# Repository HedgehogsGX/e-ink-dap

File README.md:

# e-ink-dap
DIY ESP32-S3 e-paper music player (DAP): firmware, bring-up tests and notes

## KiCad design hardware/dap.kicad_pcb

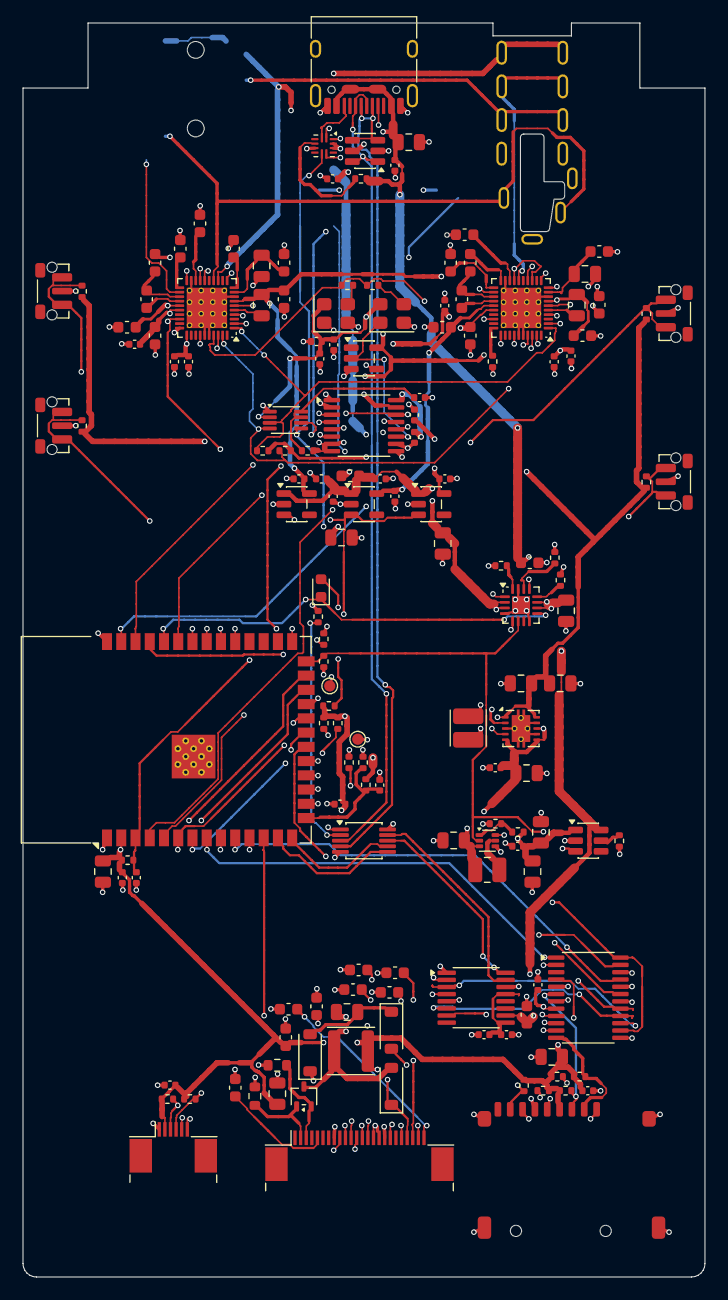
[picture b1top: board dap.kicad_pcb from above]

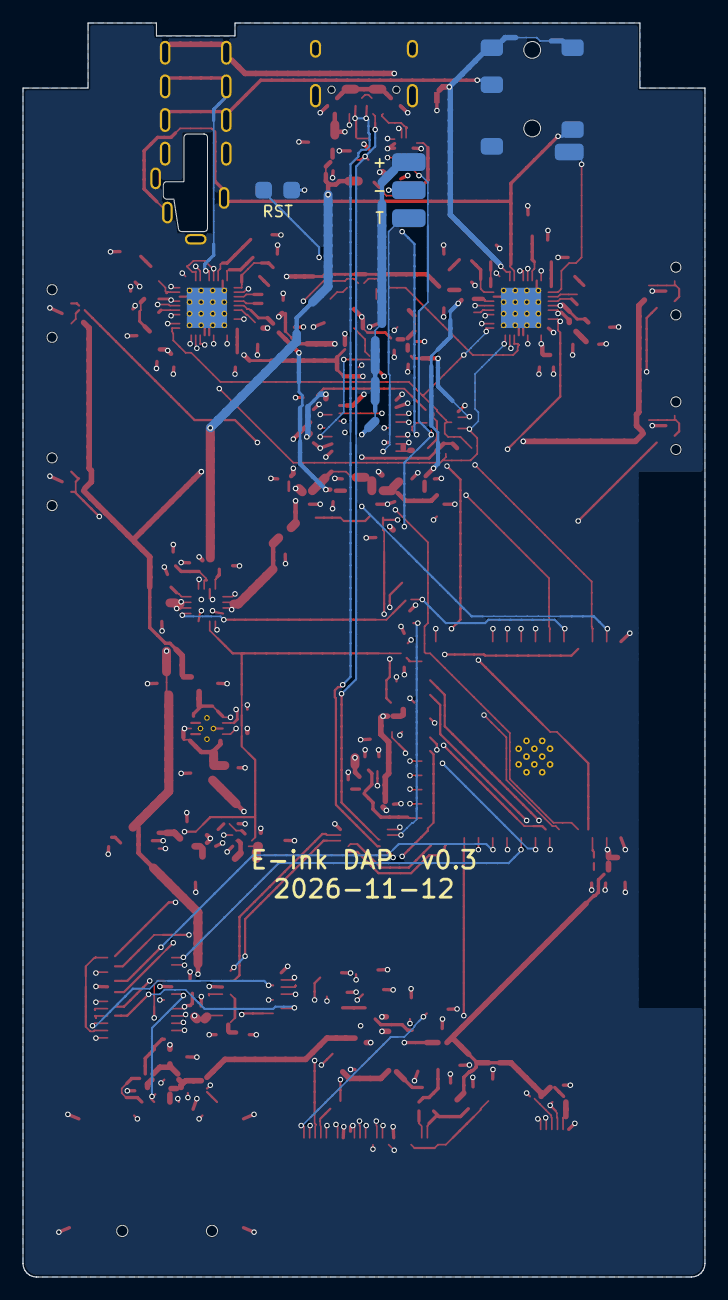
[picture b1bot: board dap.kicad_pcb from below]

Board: 6 copper layers, 60.8 x 111.8 mm, 157 parts (4 on the bottom side), 124 nets.

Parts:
C1: 1uF; C_0603_1608Metric
C2, C3, C4, C14, C15, C19, C34, C42: 10uF; C_0805_2012Metric
C5, C18, C20, C22, C35, C36, C37, C40, C41, C43, C44, C45, C46, C47, C48, C49, C50, C51, C52, C64, C65, C66: 100nF; C_0402_1005Metric
C6, C7, C16, C17, C55, C56, C69, C70: 22uF; C_0805_2012Metric
C8, C9, C10, C11, C12, C13, C21, C33, C39: 1uF; C_0402_1005Metric
C23, C24: 4.7uF/50V; C_0805_2012Metric
C25, C26, C27, C28, C29, C30, C31, C32: 1uF/50V; C_0603_1608Metric
C38, C53, C67: 4.7uF; C_0603_1608Metric
C54, C57, C58, C59, C60, C61, C62, C63, C68, C71, C72, C73, C74, C75, C76, C77: 2.2uF; C_0603_1608Metric
D1: green; LED_0603_1608Metric
D2, D3, D4: MBR0530; D_SOD-123
FB1: 600R@100MHz; L_0603_1608Metric
J1: Battery; Battery_Pads_1x03
J2: E-paper FPC; Jushuo_AFC07-S24FCA-00_1x24-1MP_P0.50_Horizontal
J3: Touch FPC; Jushuo_AFC07-S06FCA-00_1x6-1MP_P0.50_Horizontal
J4: USB-C; USB_C_Receptacle_HRO_TYPE-C-31-M-12
J5: microSD; microSD_TF-01A
J6: PJ-342; Jack_3.5mm_PJ-342
J7: KH-PJ-44002-12DBAP-A; Jack_4.4mm_KH-PJ-44002-12DBAP-A
JP1: Reset; Reset_Pads_1x02
L1: 2.2uH; L_Cenker_CKCS3015
L2: 1uH; L_1008_2520Metric
L3: 10uH; L_Changjiang_FNR4020S
NT1: NetTie; NetTie-2_SMD_Pad0.5mm
Q1: Si1308EDL; SOT-323_SC-70
R1: 1.1k; R_0402_1005Metric
R2: 1.62k; R_0402_1005Metric
R3: 68k; R_0402_1005Metric
R4: 768k; R_0402_1005Metric
R5, R8, R9, R10, R11, R13, R14, R15: 100k; R_0402_1005Metric
R6: 47k; R_0402_1005Metric
R7, R12, R23, R24, R26, R27, R28, R29, R30: 10k; R_0402_1005Metric
R16, R17: 1M; R_0402_1005Metric
R18, R19, R32, R33: 4.7k; R_0402_1005Metric
R20: 1k; R_0402_1005Metric
R21: 1M; R_0603_1608Metric
R22: 0.47; R_0603_1608Metric
R25: 887k; R_0402_1005Metric
R31: 200k; R_0402_1005Metric
R34, R35: 22; R_0402_1005Metric
R36: 4.99k; R_0402_1005Metric
SW1: Play; SW_Push_1P1T-MP_NO_Horizontal_Alps_SKRTLAE010
SW2: Power; SW_Push_1P1T-MP_NO_Horizontal_Alps_SKRTLAE010
SW3: Vol+; SW_Push_1P1T-MP_NO_Horizontal_Alps_SKRTLAE010
SW4: Vol-; SW_Push_1P1T-MP_NO_Horizontal_Alps_SKRTLAE010
TP1: TX; TestPoint_Pad_D1.0mm
TP2: GND; TestPoint_Pad_D1.0mm
U1: BQ24073RGTR; VQFN-16-1EP_3x3mm_P0.5mm_EP1.6x1.6mm
U2: TPS63001DRCR; Texas_DRC0010J_ThermalVias
U3, U4, U5: LP5907MFX-1.8; SOT-23-5
U6: TPS61023DRLR; SOT-563
U7: TPS2553DBVR; SOT-23-6
U8: ESP32-S3-WROOM-1-N16R8; ESP32-S3-WROOM-1
U9: USBLC6-2SC6; SOT-23-6
U10: TUSB320LIRWBR; Texas_X2QFN-12_1.6x1.6mm_P0.4mm
U11: FSUSB42MUX; MSOP-10_3x3mm_P0.5mm
U12: GL823K-HCY04; SSOP-16_3.9x4.9mm_P0.635mm
U13: TS3A27518EPWR; TSSOP-24_4.4x7.8mm_P0.65mm
U14: SN74AVC4T774PWR; TSSOP-16_4.4x5mm_P0.65mm
U15: PCA9306DCUR; VSSOP-8_2.3x2mm_P0.5mm
U16: 74LVC1G04; SOT-23-5
U17, U18: CS43131-CNZR; QFN-40-1EP_5x5mm_P0.4mm_EP3.6x3.6mm_ThermalVias
Y1: 22.5792MHz; Oscillator_SMD_Abracon_ASE-4Pin_3.2x2.5mm
Y2: 24.576MHz; Oscillator_SMD_Abracon_ASE-4Pin_3.2x2.5mm

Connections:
1V8_A: C11.1, C54.1, C55.2, C68.1, C69.2, U3.5, U17.7, U18.7
1V8_CP: C12.1, C59.1, C73.1, U4.5, U17.25, U18.25
1V8_D: C13.1, C45.1, C47.1, C48.1, C49.1, C50.1, C51.1, C64.1, C65.1, R32.1, R33.1, U5.5, U14.15, U15.2, U16.5, U17.4, U17.31, U18.4, U18.31, Y1.4, Y2.4
5V_BOOST: C16.1, C17.1, C18.1, R4.1, U6.6, U7.1
+3V3: C6.1, C7.1, C19.1, C20.1, C23.1, C26.1, C33.1, C36.1, C37.1, C41.1, C42.1, C43.1, C44.1, J2.15, J2.16, J3.2, J5.4, L3.1, R7.1, R12.1, R13.1, R14.1, R15.1, R18.1, R19.1, R20.1, R23.1, R24.1, R26.1, R27.1, R28.1, R29.1, R30.1, R31.1, U2.1, U2.10, U8.2, U10.12, U11.1, U13.8, U14.7, U14.8, U14.16
/Audio/DACL_FILTN: C56.1, U17.6
/Audio/DACL_FILTP: C55.1, U17.5
/Audio/DACL_FLYC_VCP: C62.2, C63.1, U17.23
/Audio/DACL_FLYN_VA: C58.2, U17.11
/Audio/DACL_FLYN_VCP: C63.2, U17.20
/Audio/DACL_FLYP_VA: C58.1, U17.10
/Audio/DACL_FLYP_VCP: C62.1, U17.24
/Audio/DACL_NVA: C56.2, C57.1, U17.9
/Audio/DACL_VCPF_N: C61.1, U17.18
/Audio/DACL_VCPF_P: C60.1, U17.21
/Audio/DACR_ADR: R36.1, U18.30
/Audio/DACR_FILTN: C70.1, U18.6
/Audio/DACR_FILTP: C69.1, U18.5
/Audio/DACR_FLYC_VCP: C76.2, C77.1, U18.23
/Audio/DACR_FLYN_VA: C72.2, U18.11
/Audio/DACR_FLYN_VCP: C77.2, U18.20
/Audio/DACR_FLYP_VA: C72.1, U18.10
/Audio/DACR_FLYP_VCP: C76.1, U18.24
/Audio/DACR_NVA: C70.2, C71.1, U18.9
/Audio/DACR_VCPF_N: C75.1, U18.18
/Audio/DACR_VCPF_P: C74.1, U18.21
/Audio/DET_35: J6.4, U17.22
/Audio/DET_44: J7.11, U18.22
/Audio/HP_GND: J6.2, J6.5, J7.1, J7.6, NT1.1, U17.13, U17.17, U18.13, U18.17
/Audio/I2C_SCL_1V8: R33.2, U15.3, U17.1, U18.1
/Audio/I2C_SDA_1V8: R32.2, U15.4, U17.39, U18.39
/Audio/I2C_VREF2: C46.1, R31.2, U15.7, U15.8
/Audio/LRCK_1V8: U14.13, U17.38, U18.38
/Audio/MCLK: R34.2, R35.2, U17.37, U18.37
/Audio/MCLK_48: R35.1, Y2.3
/Audio/MCLK_441: R34.1, Y1.3
/Audio/OSC_SEL_1V8: U14.11, U16.2, Y2.1
/Audio/OSC_SEL_N: U16.4, Y1.1
/Audio/OUT_LN: J7.4, J7.9, U17.16
/Audio/OUT_LP: J6.3, J7.5, J7.10, U17.14
/Audio/OUT_RN: J7.2, J7.7, U18.16
/Audio/OUT_RP: J6.6, J7.3, J7.8, U18.14
/Audio/SCLK_1V8: U14.14, U17.34, U18.34
/Audio/SDIN_1V8: U14.12, U17.2, U18.2
/Display/EPD_GDR: J2.2, Q1.1, R21.1
/Display/EPD_NEG: C24.2, D3.2, D4.1
/Display/EPD_RESE: J2.3, Q1.2, R22.1
/Display/EPD_SW: C24.1, D2.2, L3.2, Q1.3
/Display/EPD_VCOM: C32.1, J2.24
/Display/EPD_VDD: C27.1, J2.18
/Display/EPD_VGH: C29.1, D2.1, J2.21
/Display/EPD_VGL: C31.1, D4.2, J2.23
/Display/EPD_VSH1: C28.1, J2.20
/Display/EPD_VSH2: C25.1, J2.5
/Display/EPD_VSL: C30.1, J2.22
/MCU/CHG_LED_A: D1.2, R20.2
/MCU/DEBUG_TX: TP1.1, U8.37
/MCU/ESP_EN: C21.1, JP1.1, R7.2, U8.3
/MCU/KEY_PLAY: R12.2, SW1.1, U8.27
/MCU/KEY_POWER: R13.2, SW2.1, U8.39
/MCU/KEY_VOLDN: R15.2, SW4.1, U8.34
/MCU/KEY_VOLUP: R14.2, SW3.1, U8.33
/MCU/VBAT_SENSE: C22.1, R16.2, R17.1, U8.15
/Power/BAT_NTC: J1.3, U1.1
/Power/BB_L1: L1.1, U2.4
/Power/BB_L2: L1.2, U2.2
/Power/BST_FB: R4.2, R5.1, U6.1
/Power/BST_SW: L2.2, U6.5
/Power/CHG_ILIM: R2.1, U1.12
/Power/CHG_ISET: R1.1, U1.16
/Power/CHG_TMR: R3.1, U1.14
/Power/SW_ILIM: R6.1, U7.5
/USB and storage/GL_CLK: U12.4, U13.11
/USB and storage/GL_CMD: U12.5, U13.13
/USB and storage/GL_D0: U12.3, U13.15
/USB and storage/GL_D1: U12.2, U13.17
/USB and storage/GL_D2: U12.7, U13.18
/USB and storage/GL_D3: U12.6, U13.16
/USB and storage/GL_DM: U11.8, U12.16
/USB and storage/GL_DP: U11.9, U12.15
/USB and storage/SDC_CLK: J5.5, U13.4
/USB and storage/SDC_CMD: J5.3, R26.2, U13.6
/USB and storage/SDC_D0: J5.7, R27.2, U13.7
/USB and storage/SDC_D1: J5.8, R28.2, U13.9
/USB and storage/SDC_D2: J5.1, R29.2, U13.10
/USB and storage/SDC_D3: J5.2, R30.2, U13.12
/USB and storage/TUSB_VDET: R25.2, U10.4
/USB and storage/USB_CC1: J4.A5, U10.1
/USB and storage/USB_CC2: J4.B5, U10.2
/USB and storage/USB_DM: J4.A7, J4.B7, U9.3, U9.4, U11.4
/USB and storage/USB_DP: J4.A6, J4.B6, U9.1, U9.6, U11.3
AUDIO_EN: R9.1, U3.3, U4.3, U5.3, U8.16
BOOST_EN: R8.1, U1.6, U6.2, U7.3, U8.26
CHG_N: D1.1, U1.9, U8.36
DAC_RST: R11.1, U8.32, U17.28, U18.28
EPD_BUSY: J2.9, U8.21
EPD_CS: J2.12, U8.18
EPD_DC: J2.11, U8.17
EPD_MOSI: J2.14, U8.19
EPD_RST: J2.10, U8.12
EPD_SCK: J2.13, U8.20
ESP_USB_DM: U8.13, U11.6
ESP_USB_DP: U8.14, U11.7
GL_3V3: C39.1, C40.1, U12.9, U12.13
GND: C1.2, C2.2, C3.2, C4.2, C5.2, C6.2, C7.2, C8.2, C9.2, C10.2, C11.2, C12.2, C13.2, C14.2, C15.2, C16.2, C17.2, C18.2, C19.2, C20.2, C21.2, C22.2, C23.2, C25.2, C26.2, C27.2, C28.2, C29.2, C30.2, C31.2, C32.2, C33.2, C34.2, C35.2, C36.2, C37.2, C38.2, C39.2, C40.2, C41.2, C42.2, C43.2, C44.2, C45.2, C46.2, C47.2, C48.2, C49.2, C50.2, C51.2, C52.2, C53.2, C54.2, C57.2, C59.2, C60.2, C61.2, C64.2, C65.2, C66.2, C67.2, C68.2, C71.2, C73.2, C74.2, C75.2, D3.1, J1.2, J2.8, J2.17, J3.1, J4.A1, J4.A12, J4.B1, J4.B12, J4.SH, J5.6, J5.SH, J7.12, JP1.2, NT1.2, R1.2, R2.2, R3.2, R5.2, R6.2, R8.2, R9.2, R10.2, R11.2, R17.2, R21.2, R22.2, R36.2, SW1.2, SW2.2, SW3.2, SW4.2, TP2.1, U1.4, U1.8, U1.15, U1.17, U2.3, U2.7, U2.9, U2.11, U3.2, U4.2, U5.2, U6.4, U7.2, U8.1, U8.40, U8.41, U9.2, U10.5, U10.10, U10.11, U11.5, U11.10, U12.1, U12.14, U13.5, U13.20, U14.1, U14.2, U14.9, U14.10, U15.1, U16.3, U17.8, U17.19, U17.30, U17.35, U17.36, U17.41, U18.8, U18.19, U18.35, U18.36, U18.41, Y1.2, Y2.2
I2C_SCL: J3.6, R19.2, U8.7, U10.8, U15.6
I2C_SDA: J3.5, R18.2, U8.6, U10.7, U15.5
I2S_LRCK: U8.4, U14.4
I2S_SCLK: U8.38, U14.3
I2S_SDOUT: U8.5, U14.5
OSC_SEL: U8.35, U14.6
SD_CLK: U8.22, U13.2
SD_CMD: U8.8, U13.1
SD_D0: U8.9, U13.23
SD_D1: U8.10, U13.21
SD_D2: U8.11, U13.19
SD_D3: U8.23, U13.22
SYS: C2.1, C4.1, C5.1, C8.1, C9.1, C10.1, C15.1, FB1.1, L2.1, U1.5, U1.10, U1.11, U2.5, U2.6, U2.8, U3.1, U4.1, U5.1, U6.3
TP_INT: J3.4, R24.2, U8.24
TP_RST: J3.3, R23.2, U8.25
USB_DISK: R10.1, U8.31, U11.2, U13.14, U13.24
VBAT: C3.1, J1.1, R16.1, U1.2, U1.3
VBUS: C1.1, C34.1, C35.1, C38.1, J4.A4, J4.A9, J4.B4, J4.B9, R25.1, U1.13, U7.6, U9.5, U12.10
VP: C14.1, C52.1, C53.1, C66.1, C67.1, FB1.2, U17.26, U18.26

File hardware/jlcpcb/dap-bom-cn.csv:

Comment,Designator,Footprint,商品编号
1uF,C1,0603,C15849
10uF,"C2,C3,C4,C14,C15,C19,C35,C43",0805,C15850
100nF,"C5,C18,C20,C22,C36,C37,C38,C41,C42,C44,C45,C46,C47,C48,C49,C50,C51,C52,C53,C65,C66,C67",0402,C1525
22uF,"C6,C7,C16,C17,C56,C57,C70,C71",0805,C45783
1uF,"C8,C9,C10,C11,C12,C13,C21,C34,C40",0402,C52923
4.7uF/50V,"C23,C24",0805,C98192
1uF/50V,"C25,C26,C27,C28,C29,C30,C31,C32,C33",0603,C15849
4.7uF,"C39,C54,C68",0603,C19666
2.2uF,"C55,C58,C59,C60,C61,C62,C63,C64,C69,C72,C73,C74,C75,C76,C77,C78",0603,C23630
green,D1,0603,C72043
MBR0530,"D2,D3,D4",D_SOD-123,C77336
600R@100MHz,FB1,0603,C85833
E-paper FPC,J2,Jushuo_AFC07-S24FCA-00_1x24-1MP_P0.50_Horizontal,C262567
Touch FPC,J3,Jushuo_AFC07-S06FCA-00_1x6-1MP_P0.50_Horizontal,C262553
USB-C,J4,USB_C_Receptacle_HRO_TYPE-C-31-M-12,C165948
microSD,J5,microSD_TF-01A,C91145
2.2uH,L1,L_Cenker_CKCS3015,C354563
1uH,L2,L_Cenker_CKCS252010,C354542
10uH,L3,L_Cenker_CKCS3015,C354566
Si1308EDL,Q1,SOT-323_SC-70,C469327
1.1k,R1,0402,C25860
1.62k,R2,0402,C61897
68k,R3,0402,C36871
768k,R4,0402,C27017
100k,"R5,R8,R9,R10,R11,R13,R14,R15",0402,C25741
47k,R6,0402,C25792
10k,"R7,R12,R23,R24,R26,R27,R28,R29,R30",0402,C25744
1M,"R16,R17",0402,C26083
4.7k,"R18,R19,R32,R33",0402,C25900
1k,R20,0402,C11702
1M,R21,0603,C22935
0.47,R22,0603,C23411
887k,R25,0402,C423127
200k,R31,0402,C25764
22,"R34,R35",0402,C25092
4.99k,R36,0402,C25903
Play,SW1,SW_Push_1P1T-MP_NO_Horizontal_Alps_SKRTLAE010,C110293
Power,SW2,SW_Push_1P1T-MP_NO_Horizontal_Alps_SKRTLAE010,C110293
Vol+,SW3,SW_Push_1P1T-MP_NO_Horizontal_Alps_SKRTLAE010,C110293
Vol-,SW4,SW_Push_1P1T-MP_NO_Horizontal_Alps_SKRTLAE010,C110293
BQ24073RGTR,U1,VQFN-16-1EP_3x3mm_P0.5mm_EP1.6x1.6mm,C15220
TPS63001DRCR,U2,Texas_DRC0010J_ThermalVias,C28060
LP5907MFX-1.8,"U3,U4,U5",SOT-23-5,C92498
TPS61023DRLR,U6,SOT-563,C919459
TPS2553DBVR,U7,SOT-23-6,C55266
ESP32-S3-WROOM-1-N16R8,U8,ESP32-S3-WROOM-1,C2913202
USBLC6-2SC6,U9,SOT-23-6,C7519
TUSB320LIRWBR,U10,Texas_X2QFN-12_1.6x1.6mm_P0.4mm,C2836598
FSUSB42MUX,U11,MSOP-10_3x3mm_P0.5mm,C11355
GL823K-HCY04,U12,SSOP-16_3.9x4.9mm_P0.635mm,C284879
TS3A27518EPWR,U13,TSSOP-24_4.4x7.8mm_P0.65mm,C443721
SN74AVC4T774PWR,U14,TSSOP-16_4.4x5mm_P0.65mm,C129363
PCA9306DCUR,U15,VSSOP-8_2.3x2mm_P0.5mm,C33196
74LVC1G04,U16,SOT-23-5,C33962550
CS43131-CNZR,"U17,U18",QFN-40-1EP_5x5mm_P0.4mm_EP3.6x3.6mm_ThermalVias,C965907
22.5792MHz,Y1,Oscillator_SMD_Abracon_ASE-4Pin_3.2x2.5mm,C2901572
24.576MHz,Y2,Oscillator_SMD_Abracon_ASE-4Pin_3.2x2.5mm,C2901574

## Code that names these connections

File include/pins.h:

// Phase 1 prototype pin map — the only place GPIO numbers are defined.
//
// Board:   ESP32-S3-DevKitC-1 N16R8 (WROOM-1, quad flash + octal PSRAM, 3.3 V I/O)
// Screen:  GDEY037T03-T02 (UC8253 + FT6336U touch) on ESP32-FTS02, switch at 0.47 Ω
// Audio:   CS4398 I2S DAC board (self-configuring, no I2C)
// Storage: pass-through microSD breakout, 4-bit SDMMC
//
// Never used: 0, 3, 45, 46 (strapping), 19-20 (USB), 26-32 (flash),
// 33-37 (octal PSRAM), 43-44 (UART0 / upload port), and the RGB LED pin.
#pragma once

// Which of GPIO38/48 drives the onboard RGB LED depends on the board revision.
// 0  = not confirmed yet: the blink test toggles both so you can see which one lights.
// 10 = v1.0 (LED on 48), 11 = v1.1 (LED on 38).
// This board: v1.1, confirmed 2026-10-16 (selftest LED lit red on GPIO38).
#ifndef DEVKITC_REV
#define DEVKITC_REV 11
#endif

#if DEVKITC_REV == 11
constexpr int PIN_BOARD_LED = 38;
constexpr int PIN_FREE_38_48 = 48;
#elif DEVKITC_REV == 10
constexpr int PIN_BOARD_LED = 48;
constexpr int PIN_FREE_38_48 = 38;
#else
constexpr int PIN_BOARD_LED = -1;
constexpr int PIN_FREE_38_48 = -1;
#endif

// E-paper, SPI (10/11/12 are the FSPI IO_MUX pins). Comments give the pin on the
// FTS02's Raspberry Pi socket (FTS02 schematic 20250819). Power: socket pin 1 = 3V3,
// pin 6 = GND. Socket pins 2/4 (5 V) stay empty: the panel and touch run on 3.3 V.
constexpr int PIN_EPD_CS   = 10;  // socket 24 "CS"
constexpr int PIN_EPD_MOSI = 11;  // socket 19 "SPI_MOSI"
constexpr int PIN_EPD_SCK  = 12;  // socket 23 "SPI_SCK"
constexpr int PIN_EPD_DC   = 9;   // socket 22 "D/C"
constexpr int PIN_EPD_RST  = 8;   // socket 11 "RES"
constexpr int PIN_EPD_BUSY = 13;  // socket 18 "BUSY". UC8253: 0 = busy, 1 = idle

// Touch, FT6336U on I2C (address 0x38), touch cable in the FTS02's TP-FPC2
constexpr int PIN_TOUCH_SDA = 6;   // socket 33 "TP_SDA"
constexpr int PIN_TOUCH_SCL = 7;   // socket 31 "TP_SCL"
constexpr int PIN_TOUCH_INT = 47;  // socket 35 "TP_INT"
constexpr int PIN_TOUCH_RST = PIN_FREE_38_48;  // socket 37 "TP_RST"; set DEVKITC_REV before the touch test

// microSD, 4-bit SDMMC. 10 kΩ pull-ups to 3.3 V on CMD and D0-D3, not on CLK.
constexpr int PIN_SD_CLK = 14;
constexpr int PIN_SD_CMD = 15;
constexpr int PIN_SD_D0  = 16;
constexpr int PIN_SD_D1  = 17;
constexpr int PIN_SD_D2  = 18;
constexpr int PIN_SD_D3  = 21;

// I2S to the CS4398 board. Share GND; leave the board's 3V3_OUT unconnected.
constexpr int PIN_I2S_MCK  = 1;
constexpr int PIN_I2S_BCK  = 2;
constexpr int PIN_I2S_LRCK = 4;
constexpr int PIN_I2S_DATA = 5;

// Buttons: GPIO to one leg, GND to the other, INPUT_PULLUP, pressed = LOW.
constexpr int PIN_BTN_PLAY     = 39;
constexpr int PIN_BTN_VOL_UP   = 40;
constexpr int PIN_BTN_VOL_DOWN = 41;
constexpr int PIN_BTN_LOCK     = 42;
